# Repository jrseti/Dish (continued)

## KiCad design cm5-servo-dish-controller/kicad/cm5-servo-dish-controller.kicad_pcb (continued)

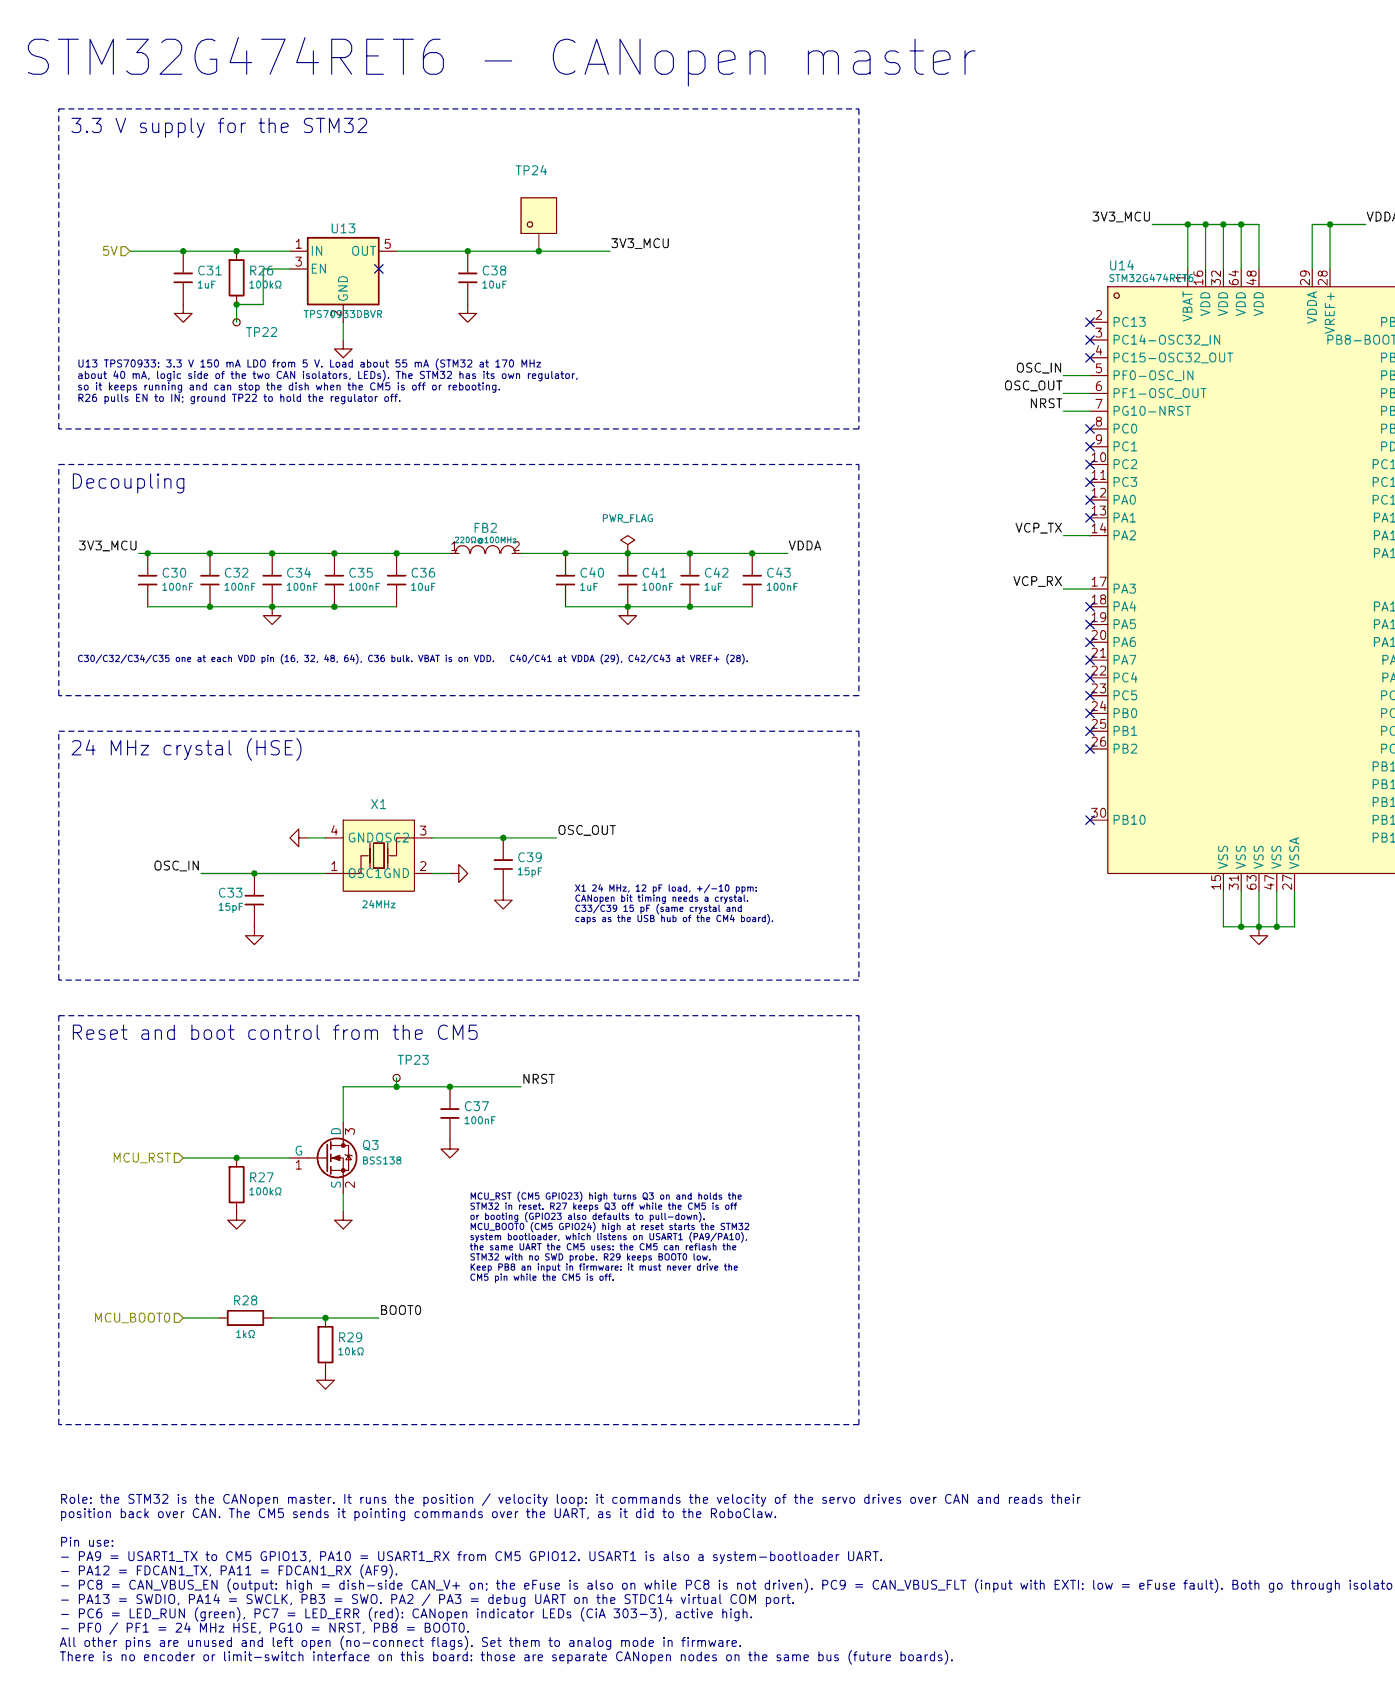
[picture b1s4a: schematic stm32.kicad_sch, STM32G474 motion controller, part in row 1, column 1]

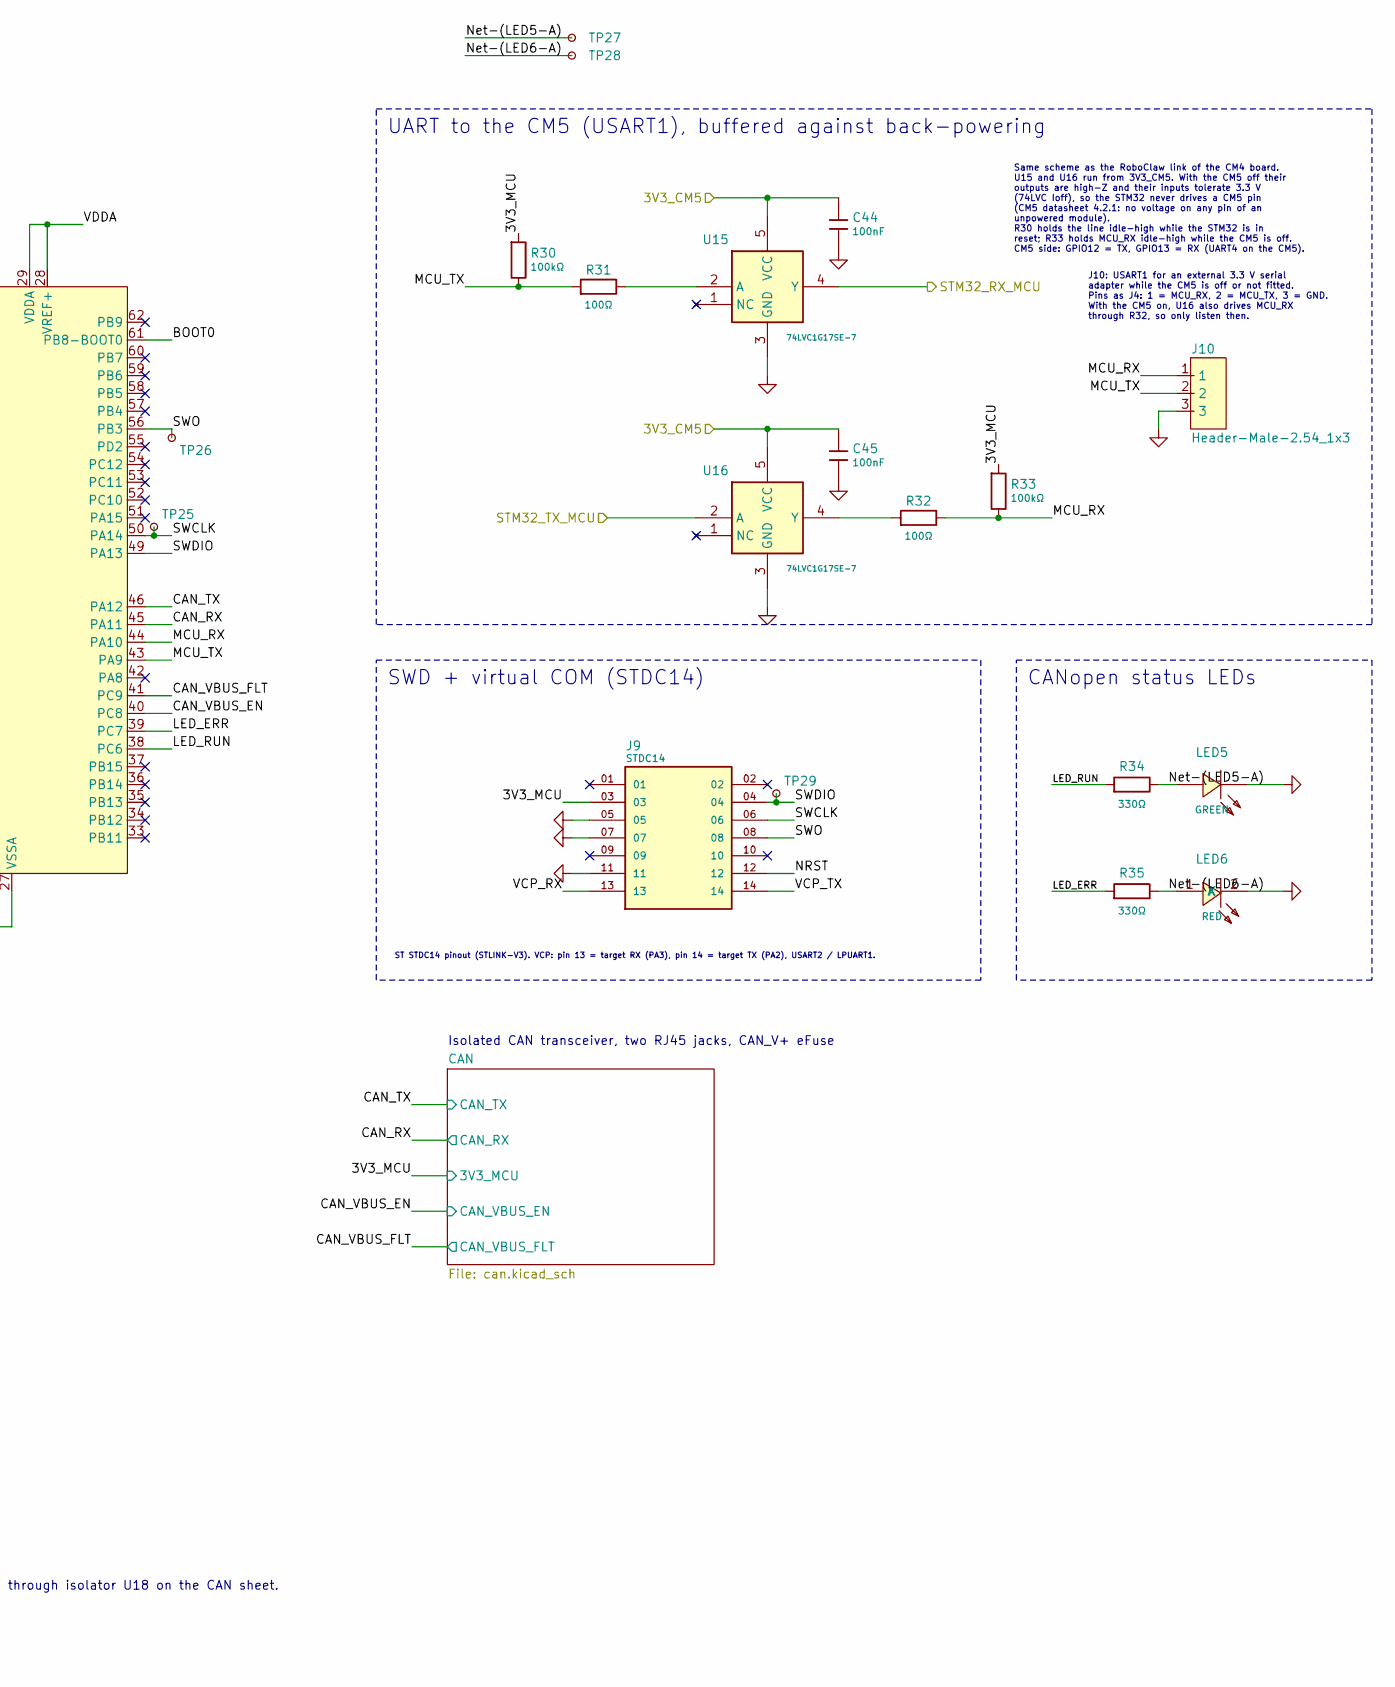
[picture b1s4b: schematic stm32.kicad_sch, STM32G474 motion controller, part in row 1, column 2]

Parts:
C30, C32, C34, C35, C37, C41, C43, C44, C45: 100nF; CAPC1005X55N; Tolerance ±10%; Voltage Rating 16V; MPN CL05B104KO5NNNC; LCSC Part C1525
C31, C40, C42: 1uF; CAPC1608X95N; Tolerance ±10%; Voltage Rating 50V; MPN CL10A105KB8NNNC; LCSC Part C15849
C33, C39: 15pF; CAPC1005X55N; Tolerance ±5%; Voltage Rating 50V; MPN 0402CG150J500NT; LCSC Part C1548
C36, C38: 10uF; CAPC1608X95N; Tolerance ±20%; Voltage Rating 25V; MPN CL10A106MA8NRNC; LCSC Part C96446
FB2: 220Ω@100MHz; INDC1608X95N; Tolerance ±25%; Current Rating 1.4A; MPN BLM18PG221SN1D; LCSC Part C80165
J9: STDC14; Samtec_FTSH-107-01-L-DV-K-A; PARTREV H; LCSC Part C5563894
J10: Header-Male-2.54_1x3; PinHeader_1x03_P2.54mm_Vertical; MPN 2.54-1*3PPin; LCSC Part C49257
LED5: GREEN; LEDC2012X110N; MPN KT-0805G; LCSC Part C2297
LED6: RED; LEDC2012X110N; MPN KT-0805R; LCSC Part C2295
Q3: BSS138; SOT95P237X112-3N; MPN BSS138; LCSC Part C7420339
R26, R27, R30, R33: 100kΩ; RESC1005X40N; Tolerance ±1%; Voltage Rating 50V; MPN 0402WGF1003TCE; LCSC Part C25741
R28: 1kΩ; RESC1005X40N; Tolerance ±1%; Voltage Rating 50V; MPN 0402WGF1001TCE; LCSC Part C11702
R29: 10kΩ; RESC1005X40N; Tolerance ±1%; Voltage Rating 50V; MPN 0402WGF1002TCE; LCSC Part C25744
R31, R32: 100Ω; RESC1005X40N; Tolerance ±1%; Voltage Rating 50V; MPN 0402WGF1000TCE; LCSC Part C25076
R34, R35: 330Ω; RESC1608X55N; Tolerance ±1%; Voltage Rating 75V; MPN 0603WAF3300T5E; LCSC Part C23138
TP22, TP23, TP25, TP26, TP27, TP28, TP29: TestPoint_Small; TestPoint_Pad_D0.8mm
TP24: 3V3_MCU; Ronghe_RH-5016; MPN RH-5016; LCSC Part C5199799
U13: TPS70933DBVR; SOT95P280X145-5N; MPN TPS70933DBVR; LCSC Part C89347
U14: STM32G474RET6; QFP50P1200X1200X160-64N; MPN STM32G474RET6; LCSC Part C521608
U15, U16: 74LVC1G17SE-7; SOT65P210X110-5N; MPN 74LVC1G17SE-7; LCSC Part C212314
X1: 24MHz; OSCCC320X250X80-4N; Frequency Tolerance ±10ppm; MPN X322524MOB4SI; LCSC Part C70590

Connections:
/3V3_CM5: C44.1, C45.1, U15.5 (VCC), U16.5 (VCC); also elsewhere on the board
/5V: C31.1, R26.1, U13.1 (IN); also elsewhere on the board
/CM5/MCU_BOOT0: R28.1; also elsewhere on the board
/CM5/MCU_RST: Q3.1 (G), R27.1; also elsewhere on the board
/CM5/STM32_RX_MCU: U15.4 (Y); also elsewhere on the board
/CM5/STM32_TX_MCU: U16.2 (A); also elsewhere on the board
/STM32/3V3_MCU: C30.1, C32.1, C34.1, C35.1, C36.1, C38.1, FB2.1, J9.03, R30.1, R33.1, TP24.1 (1_1), U13.5 (OUT), U14.1 (VBAT), U14.16 (VDD), U14.32 (VDD), U14.48 (VDD), U14.64 (VDD); also elsewhere on the board
/STM32/BOOT0: R28.2, R29.1, U14.61 (PB8-BOOT0)
/STM32/CAN_RX: U14.45 (PA11); also elsewhere on the board
/STM32/CAN_TX: U14.46 (PA12); also elsewhere on the board
/STM32/CAN_VBUS_EN: U14.40 (PC8); also elsewhere on the board
/STM32/CAN_VBUS_FLT: U14.41 (PC9); also elsewhere on the board
/STM32/LED_ERR: R35.1, U14.39 (PC7)
/STM32/LED_RUN: R34.1, U14.38 (PC6)
/STM32/MCU_RX: J10.1, R32.2, R33.2, U14.44 (PA10)
/STM32/MCU_TX: J10.2, R30.2, R31.1, U14.43 (PA9)
/STM32/NRST: C37.1, J9.12, Q3.3 (D), TP23.1 (1_1), U14.7 (PG10-NRST)
/STM32/Net-(LED5-A): LED5.1 (A), R34.2, TP27.1 (1_1)
/STM32/Net-(LED6-A): LED6.1 (A), R35.2, TP28.1 (1_1)
/STM32/OSC_IN: C33.1, U14.5 (PF0-OSC_IN), X1.1 (OSC1)
/STM32/OSC_OUT: C39.1, U14.6 (PF1-OSC_OUT), X1.3 (OSC2)
/STM32/SWCLK: J9.06, TP25.1 (1_1), U14.50 (PA14)
/STM32/SWDIO: J9.04, TP29.1 (1_1), U14.49 (PA13)
/STM32/SWO: J9.08, TP26.1 (1_1), U14.56 (PB3)
/STM32/VCP_RX: J9.13, U14.17 (PA3)
/STM32/VCP_TX: J9.14, U14.14 (PA2)
/STM32/VDDA: C40.1, C41.1, C42.1, C43.1, FB2.2, U14.28 (VREF+), U14.29 (VDDA)
GND: C30.2, C31.2, C32.2, C33.2, C34.2, C35.2, C36.2, C37.2, C38.2, C39.2, C40.2, C41.2, C42.2, C43.2, C44.2, C45.2, J9.05, J9.07, J9.11, J10.3, LED5.2 (K), LED6.2 (K), Q3.2 (S), R27.2, R29.2, U13.2 (GND), U14.15 (VSS), U14.27 (VSSA), U14.31 (VSS), U14.47 (VSS), U14.63 (VSS), U15.3 (GND), U16.3 (GND), X1.2 (GND), X1.4 (GND); also elsewhere on the board
unnamed: R26.2, TP22.1 (1_1), U13.3 (EN)
unnamed: R31.2, U15.2 (A)
unnamed: R32.1, U16.4 (Y)

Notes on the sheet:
MCU_RST (CM5 GPIO23) high turns Q3 on and holds the STM32 in reset. R27 keeps Q3 off while the CM5 is off or booting (GPIO23 also defaults to pull-down). MCU_BOOT0 (CM5 GPIO24) high at reset starts the STM32 system bootloader, which listens on USART1 (PA9/PA10), the same UART the CM5 uses: the CM5 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
C30/C32/C34/C35 one at each VDD pin (16, 32, 48, 64), C36 bulk. VBAT is on VDD. C40/C41 at VDDA (29), C42/C43 at VREF+ (28).
Isolated CAN transceiver, two RJ45 jacks, CAN_V+ eFuse
X1 24 MHz, 12 pF load, +/-10 ppm: CANopen bit timing needs a crystal. C33/C39 15 pF (same crystal and caps as the USB hub of the CM4 board).
U13 TPS70933: 3.3 V 150 mA LDO from 5 V. Load about 55 mA (STM32 at 170 MHz about 40 mA, logic side of the two CAN isolators, LEDs). The STM32 has its own regulator, so it keeps running and can stop the dish when the CM5 is off or rebooting. R26 pulls EN to IN; ground TP22 to hold the regulator off.
Role: the STM32 is the CANopen master. It runs the position / velocity loop: it commands the velocity of the servo drives over CAN and reads their position back over CAN. The CM5 sends it pointing commands over the UART, as it did to the RoboClaw. Pin use: - PA9 = USART1_TX to CM5 GPIO13, PA10 = US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
CANopen status LEDs
UART to the CM5 (USART1), buffered against back-powering
Reset and boot control from the CM5
24 MHz crystal (HSE)
ST STDC14 pinout (STLINK-V3). VCP: pin 13 = target RX (PA3), pin 14 = target TX (PA2), USART2 / LPUART1.
STM32G474RET6 - CANopen master
3.3 V supply for the STM32
Same scheme as the RoboClaw link of the CM4 board. U15 and U16 run from 3V3_CM5. With the CM5 off their outputs are high-Z and their inputs tolerate 3.3 V (74LVC Ioff), so the STM32 never drives a CM5 pin (CM5 datasheet 4.2.1: no voltage on any pin of an unpowered module). R30 holds the line idle-h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
Decoupling
SWD + virtual COM (STDC14)
J10: USART1 for an external 3.3 V serial adapter while the CM5 is off or not fitted. Pins as J4: 1 = MCU_RX, 2 = MCU_TX, 3 = GND. With the CM5 on, U16 also drives MCU_RX through R32, so only listen then.

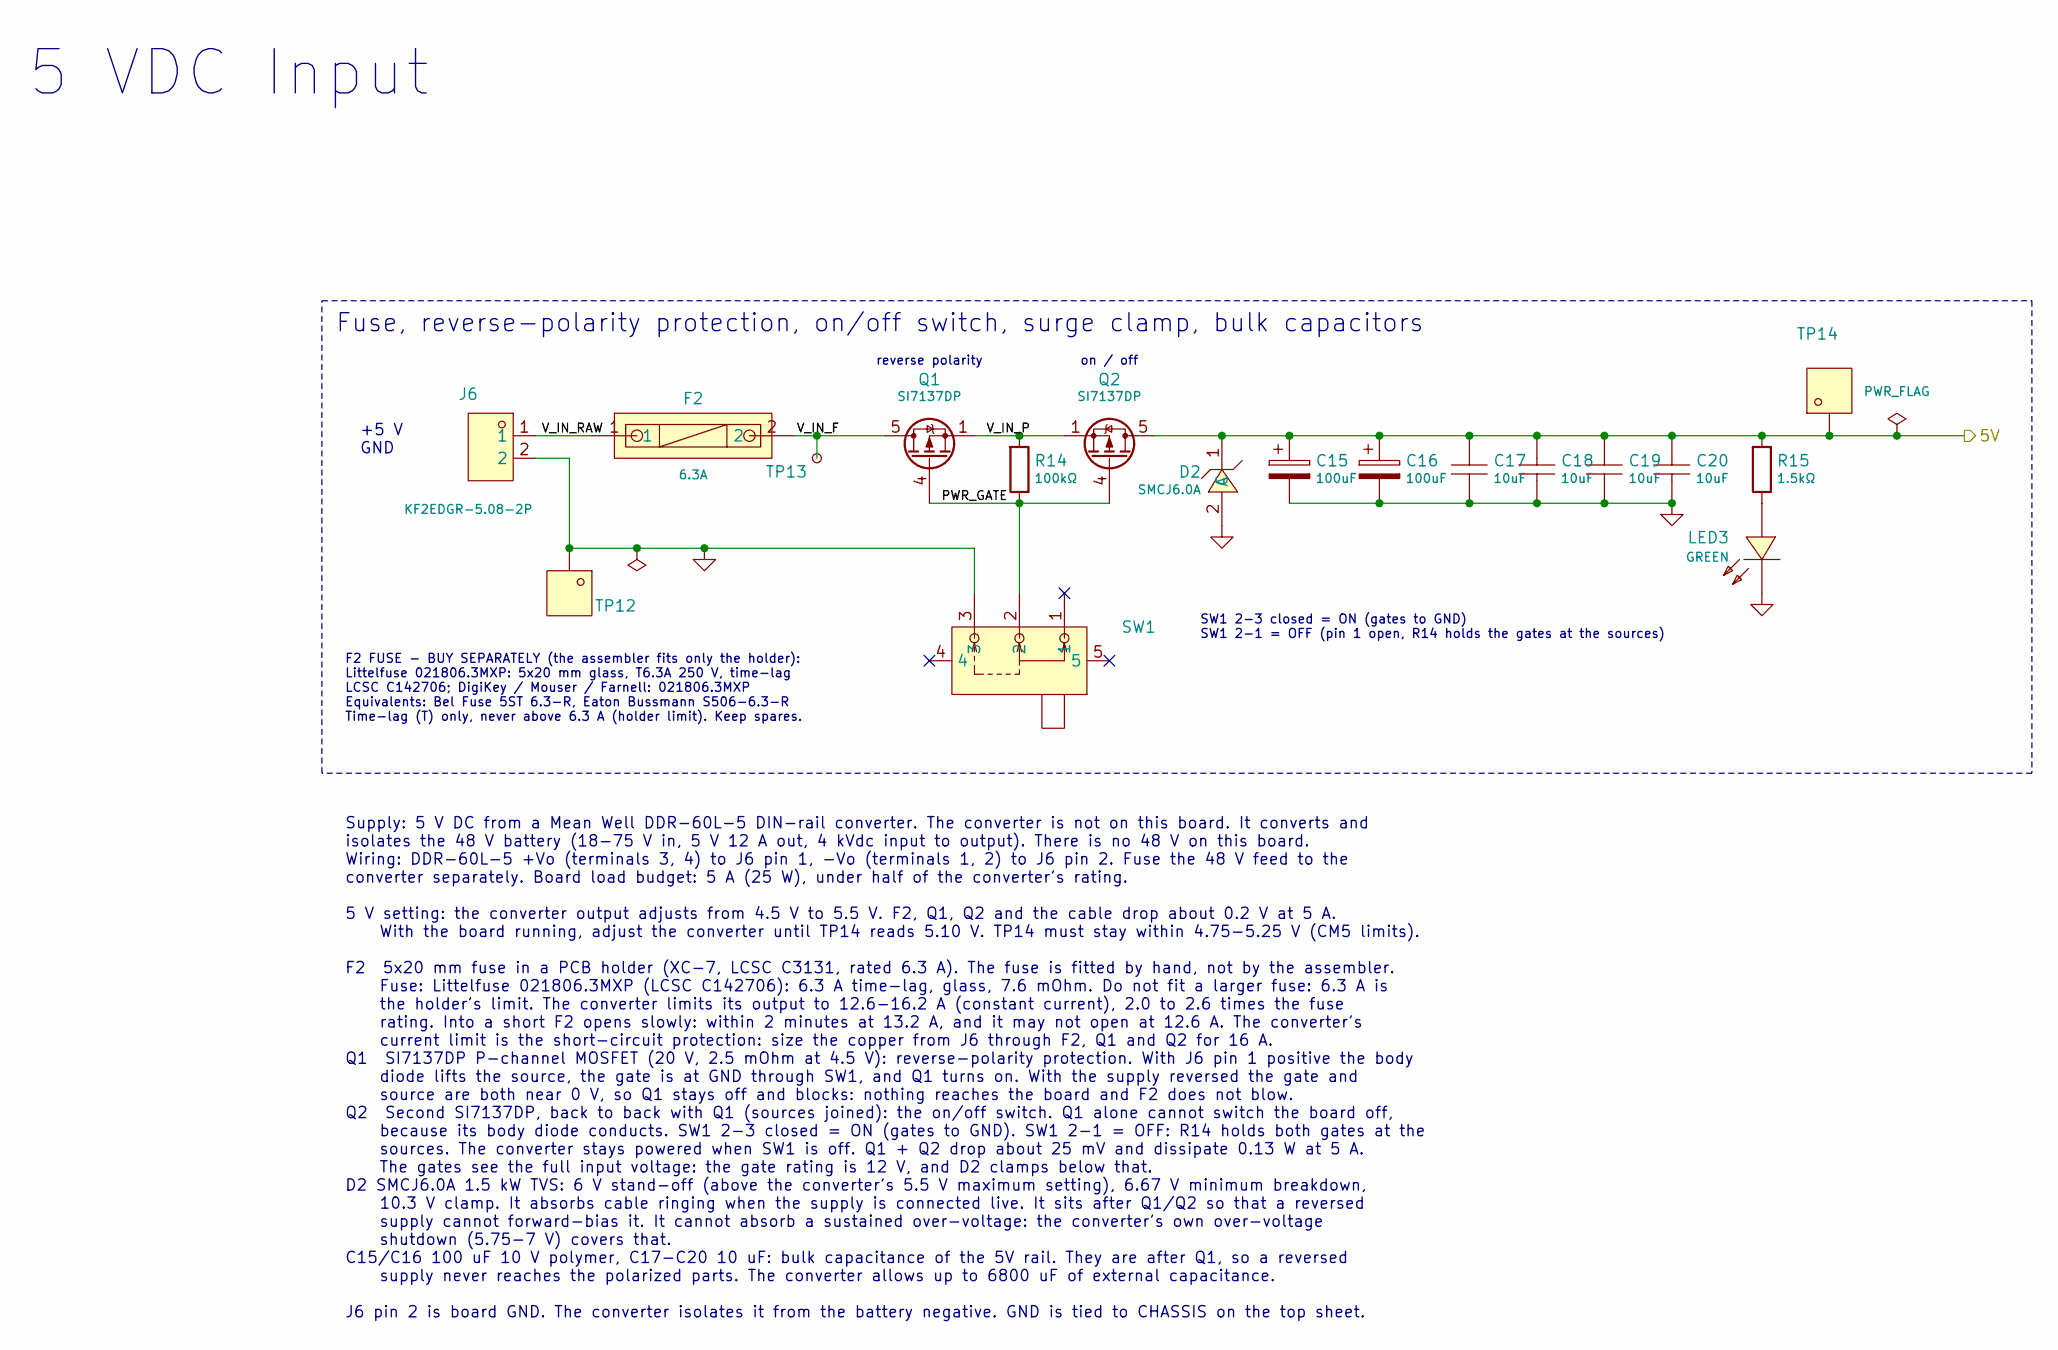
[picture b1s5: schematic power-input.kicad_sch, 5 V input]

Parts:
C15, C16: 100uF; CAPMP7343X310N; Tolerance ±20%; Voltage Rating 10V; MPN SA11AM101A19R15XXX; LCSC Part C135491
C17, C18, C19, C20: 10uF; CAPC2012X145N; Tolerance ±10%; Voltage Rating 10V; MPN CL21B106KPQNNNE; LCSC Part C32635
D2: SMCJ6.0A; DIOM7959X262N; MPN SMCJ6.0A/TR13; LCSC Part C310065
F2: 6.3A; Xucheng_XC-7_5x20; Voltage Rating 250V; Interrupting Rating 63A @ 250VAC; MPN 5x20 BLX-A XC-7; LCSC Part C3131
J6: KF2EDGR-5.08-2P; KEFA_KF2EDGR-5.08-2P; MPN KF2EDGR-5.08-2P; LCSC Part C441204
LED3: GREEN; LEDC2012X110N; MPN KT-0805G; LCSC Part C2297
Q1, Q2: SI7137DP; SON127P615X515X120-9N; MPN SI7137DP-T1-GE3; LCSC Part C784367
R14: 100kΩ; RESC1005X40N; Tolerance ±1%; Voltage Rating 50V; MPN 0402WGF1003TCE; LCSC Part C25741
R15: 1.5kΩ; RESC1005X40N; Tolerance ±1%; Voltage Rating 50V; MPN 0402WGF1501TCE; LCSC Part C25867
SW1: SS-12F49-G050; G-Switch_SS-12F49-G050; MPN SS-12F49-G050; LCSC Part C2876010
TP12: GND; Ronghe_RH-5016; MPN RH-5016; LCSC Part C5199799
TP13: TestPoint_Small; TestPoint_Pad_D0.8mm
TP14: 5V; Ronghe_RH-5016; MPN RH-5016; LCSC Part C5199799

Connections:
/5V: C15.1, C16.1, C17.1, C18.1, C19.1, C20.1, D2.1 (C), Q2.5 (D), Q2.6 (D), Q2.7 (D), Q2.8 (D), Q2.9 (D), R15.1, TP14.1 (1_1); also elsewhere on the board
/power-input/PWR_GATE: Q1.4 (G), Q2.4 (G), R14.2, SW1.2
/power-input/V_IN_F: F2.2, Q1.5 (D), Q1.6 (D), Q1.7 (D), Q1.8 (D), Q1.9 (D), TP13.1 (1_1)
/power-input/V_IN_P: Q1.1 (S), Q1.2 (S), Q1.3 (S), Q2.1 (S), Q2.2 (S), Q2.3 (S), R14.1
/power-input/V_IN_RAW: F2.1, J6.1
GND: C15.2, C16.2, C17.2, C18.2, C19.2, C20.2, D2.2 (A), J6.2, LED3.2 (K), SW1.3, TP12.1 (1_1); also elsewhere on the board
unnamed: LED3.1 (A), R15.2

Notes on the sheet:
on / off
+5 V GND
Supply: 5 V DC from a Mean Well DDR-60L-5 DIN-rail converter. The converter is not on this board. It converts and isolates the 48 V battery (18-75 V in, 5 V 12 A out, 4 kVdc input to output). There is no 48 V on this board. Wiring: DDR-60L-5 +Vo (terminals 3, 4) to J6 pin 1, -Vo (terminals 1, 2) to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
Fuse, reverse-polarity protection, on/off switch, surge clamp, bulk capacitors
5 VDC Input
SW1 2-3 closed = ON (gates to GND) SW1 2-1 = OFF (pin 1 open, R14 holds the gates at the sources)
reverse polarity
F2 FUSE - BUY SEPARATELY (the assembler fits only the holder): Littelfuse 021806.3MXP: 5x20 mm glass, T6.3A 250 V, time-lag LCSC C142706; DigiKey / Mouser / Farnell: 021806.3MXP Equivalents: Bel Fuse 5ST 6.3-R, Eaton Bussmann S506-6.3-R Time-lag (T) only, never above 6.3 A (holder limit). Keep spar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

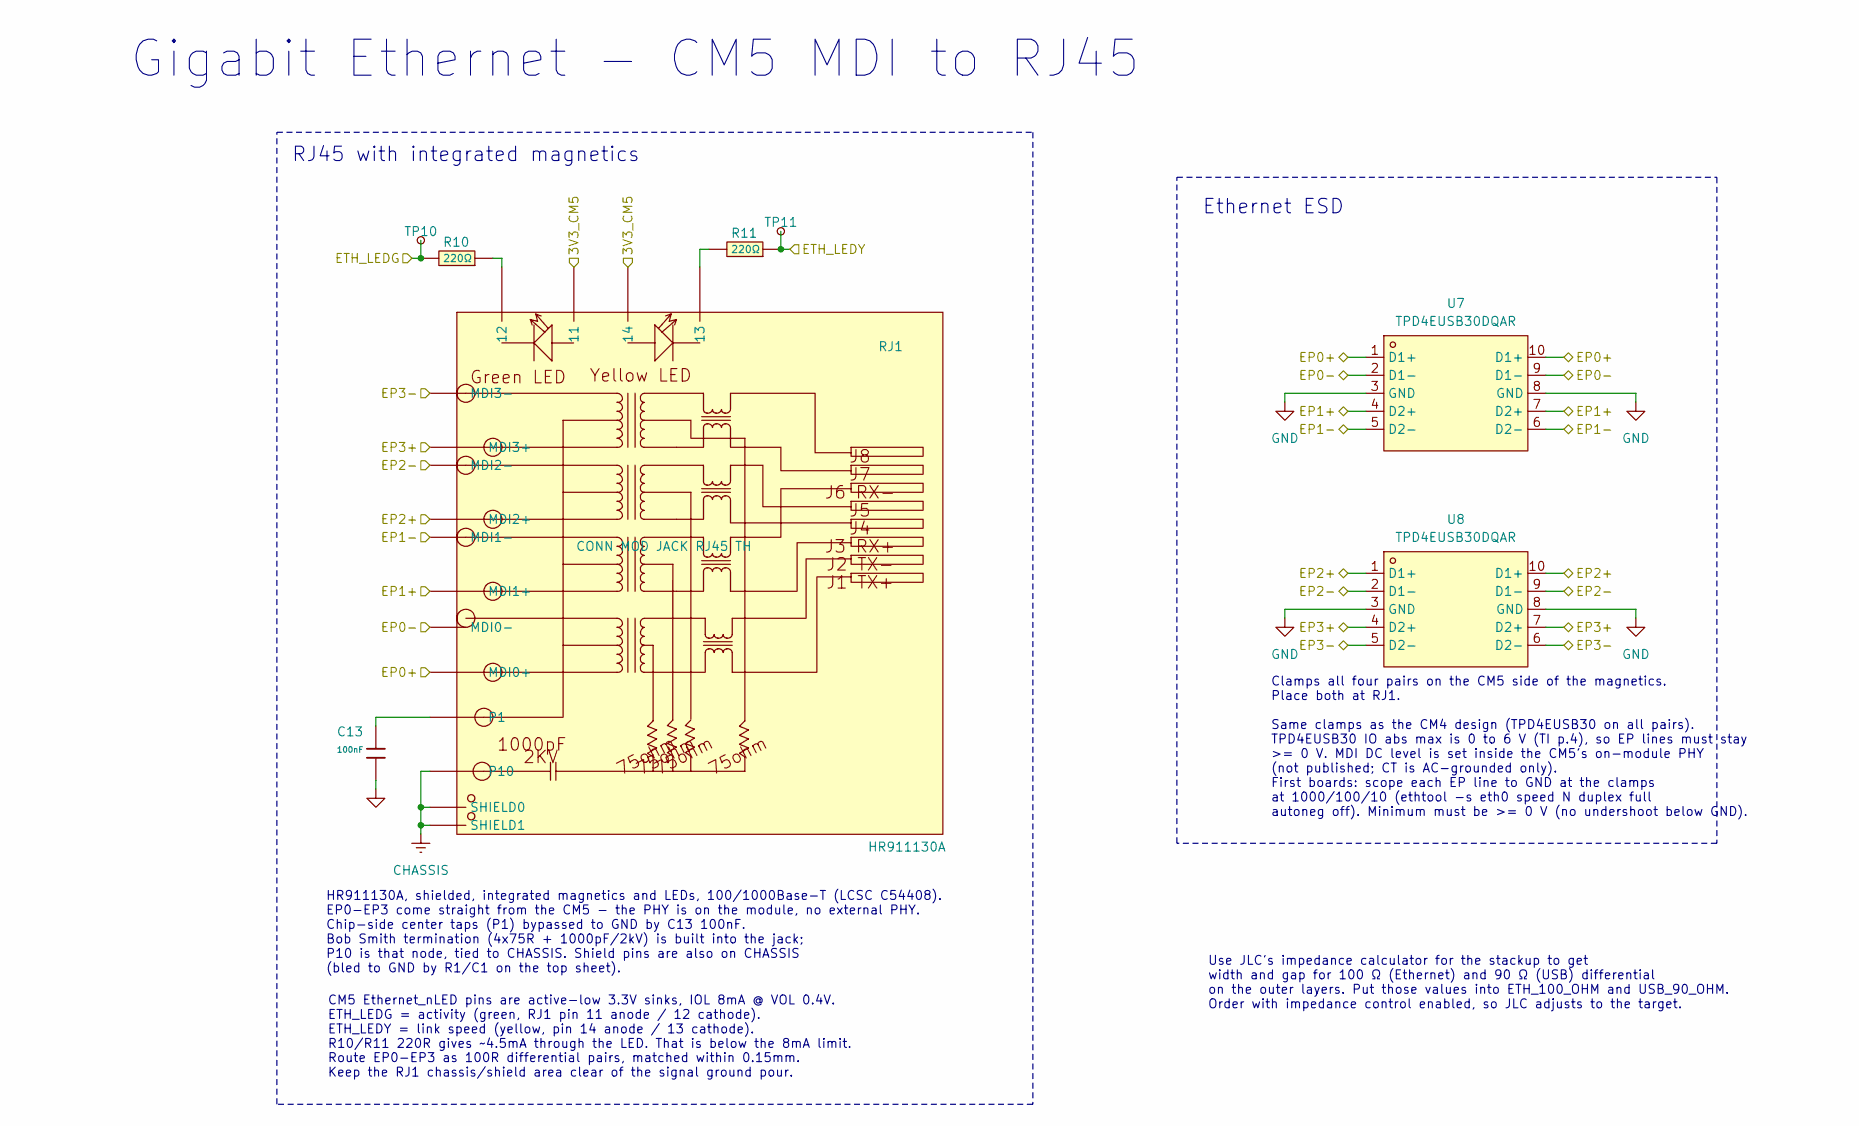
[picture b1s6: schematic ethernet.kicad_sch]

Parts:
C13: 100nF; CAPC1005X55N; Tolerance ±10%; Voltage Rating 16V; MPN CL05B104KO5NNNC; LCSC Part C1525
R10, R11: 220Ω; RESC1005X40N; Tolerance ±1%; Voltage Rating 50V; MPN 0402WGF2200TCE; LCSC Part C25091
RJ1: HR911130A; HanRun_HR911130A; MPN HR911130A; LCSC Part C54408
TP10, TP11: TestPoint_Small; TestPoint_Pad_D0.8mm
U7, U8: TPD4EUSB30DQAR; SON50P100X250X60-10N; MPN TPD4EUSB30DQAR; LCSC Part C90627

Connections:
/3V3_CM5: RJ1.11, RJ1.14; also elsewhere on the board
/CM5/EP0+: RJ1.P2 (MDI0+), U7.1 (D1+), U7.10 (D1+); also elsewhere on the board
/CM5/EP0-: RJ1.P3 (MDI0-), U7.2 (D1-), U7.9 (D1-); also elsewhere on the board
/CM5/EP1+: RJ1.P4 (MDI1+), U7.4 (D2+), U7.7 (D2+); also elsewhere on the board
/CM5/EP1-: RJ1.P7 (MDI1-), U7.5 (D2-), U7.6 (D2-); also elsewhere on the board
/CM5/EP2+: RJ1.P5 (MDI2+), U8.1 (D1+), U8.10 (D1+); also elsewhere on the board
/CM5/EP2-: RJ1.P6 (MDI2-), U8.2 (D1-), U8.9 (D1-); also elsewhere on the board
/CM5/EP3+: RJ1.P8 (MDI3+), U8.4 (D2+), U8.7 (D2+); also elsewhere on the board
/CM5/EP3-: RJ1.P9 (MDI3-), U8.5 (D2-), U8.6 (D2-); also elsewhere on the board
/CM5/ETH_LEDG: R10.2, TP10.1 (1_1); also elsewhere on the board
/CM5/ETH_LEDY: R11.1, TP11.1 (1_1); also elsewhere on the board
CHASSIS: RJ1.P10, RJ1.SHIELD0, RJ1.SHIELD1; also elsewhere on the board
GND: C13.2, U7.3 (GND), U7.8 (GND), U8.3 (GND), U8.8 (GND); also elsewhere on the board
unnamed: C13.1, RJ1.P1
unnamed: R10.1, RJ1.12
unnamed: R11.2, RJ1.13

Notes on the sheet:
Ethernet ESD
Use JLC's impedance calculator for the stackup to get width and gap for 100 Ω (Ethernet) and 90 Ω (USB) differential on the outer layers. Put those values into ETH_100_OHM and USB_90_OHM. Order with impedance control enabled, so JLC adjusts to the target.
HR911130A, shielded, integrated magnetics and LEDs, 100/1000Base-T (LCSC C54408). EP0-EP3 come straight from the CM5 - the PHY is on the module, no external PHY. Chip-side center taps (P1) bypassed to GND by C13 100nF. Bob Smith termination (4x75R + 1000pF/2kV) is built into the jack; P10 is that n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
RJ45 with integrated magnetics
Clamps all four pairs on the CM5 side of the magnetics. Place both at RJ1. Same clamps as the CM4 design (TPD4EUSB30 on all pairs). TPD4EUSB30 IO abs max is 0 to 6 V (TI p.4), so EP lines must stay >= 0 V. MDI DC level is set inside the CM5's on-module PHY (not published; CT is AC-grounded only). F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
Route EP0-EP3 as 100R differential pairs, matched within 0.15mm. Keep the RJ1 chassis/shield area clear of the signal ground pour.
CM5 Ethernet_nLED pins are active-low 3.3V sinks, IOL 8mA @ VOL 0.4V. ETH_LEDG = activity (green, RJ1 pin 11 anode / 12 cathode). ETH_LEDY = link speed (yellow, pin 14 anode / 13 cathode). R10/R11 220R gives ~4.5mA through the LED. That is below the 8mA limit.
Gigabit Ethernet - CM5 MDI to RJ45

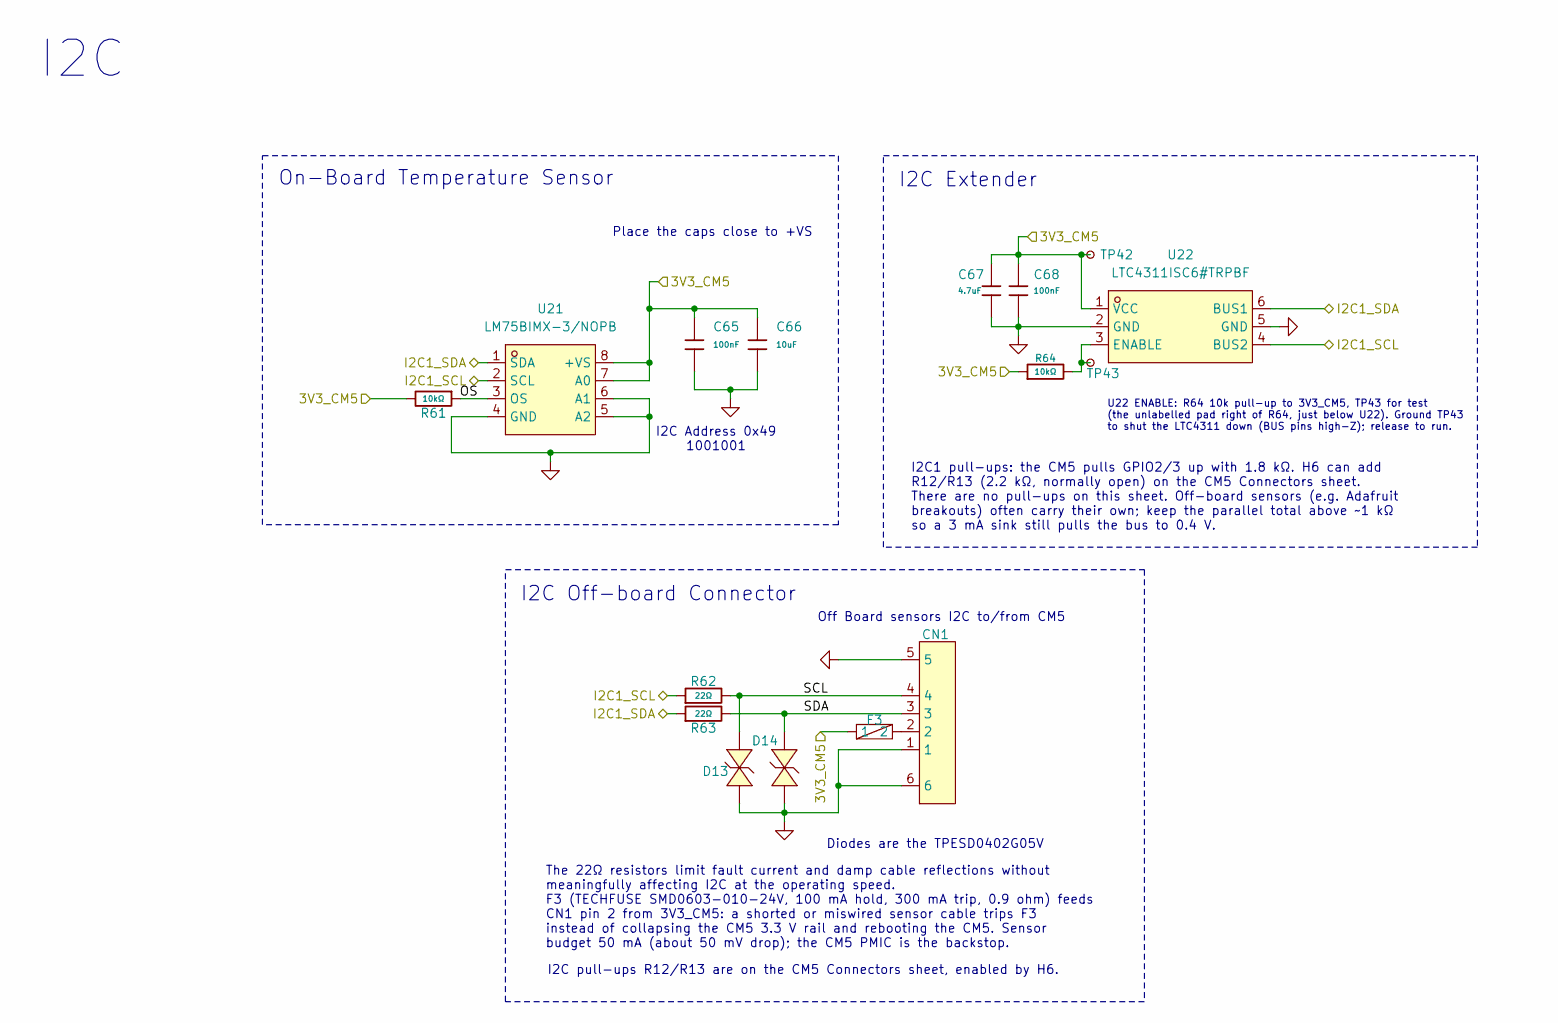
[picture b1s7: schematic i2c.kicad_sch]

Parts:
C65, C68: 100nF; CAPC1005X55N; Tolerance ±10%; Voltage Rating 16V; MPN CL05B104KO5NNNC; LCSC Part C1525
C66: 10uF; CAPC1608X95N; Tolerance ±10%; Voltage Rating 10V; MPN CL10A106KP8NNNC; LCSC Part C19702
C67: 4.7uF; CAPC1005X55N; Tolerance ±20%; Voltage Rating 10V; MPN CL05A475MP5NRNC; LCSC Part C23733
CN1: SM04B-SRSS-TB (LF)(SN); JST_SH_SM04B-SRSS-TB_1x04-1MP_P1.00mm_Horizontal; MPN SM04B-SRSS-TB(LF)(SN); LCSC Part C160404
D13, D14: TPESD0402G05V; DIOC1005X55N; MPN TPESD0402G05V; LCSC Part C558615
F3: 100mA; FUSC1608X100N; MPN SMD0603-010-24V; LCSC Part C70048
R61, R64: 10kΩ; RESC1005X40N; Tolerance ±1%; Voltage Rating 50V; MPN 0402WGF1002TCE; LCSC Part C25744
R62, R63: 22Ω; RESC1005X40N; Tolerance ±1%; Voltage Rating 50V; MPN 0402WGF220JTCE; LCSC Part C25092
TP42, TP43: TestPoint_Small; TestPoint_Pad_D0.8mm
U21: LM75BIMX-3/NOPB; SOIC127P600X175-8N; MPN LM75BIMX-3/NOPB; LCSC Part C477980
U22: LTC4311ISC6#TRPBF; SOT65P210X110-6N; MPN LTC4311ISC6#TRPBF; LCSC Part C688097

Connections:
/3V3_CM5: C65.1, C66.1, C67.1, C68.1, F3.1, R61.2, R64.1, TP42.1 (1_1), U21.7 (A0), U21.8 (+VS), U22.1 (VCC); also elsewhere on the board
/CM5/I2C1_SCL: R62.1, U21.2 (SCL), U22.4 (BUS2); also elsewhere on the board
/CM5/I2C1_SDA: R63.1, U21.1 (SDA), U22.6 (BUS1); also elsewhere on the board
/CM5/I2C/OS: R61.1, U21.3 (OS)
/CM5/I2C/SCL: CN1.4, D13.1 (K), R62.2
/CM5/I2C/SDA: CN1.3, D14.1 (K), R63.2
GND: C65.2, C66.2, C67.2, C68.2, CN1.1, CN1.5, CN1.6, D13.2 (A), D14.2 (A), U21.4 (GND), U21.5 (A2), U21.6 (A1), U22.2 (GND), U22.5 (GND); also elsewhere on the board
unnamed: CN1.2, F3.2
unnamed: R64.2, TP43.1 (1_1), U22.3 (ENABLE)

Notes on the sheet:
I2C1 pull-ups: the CM5 pulls GPIO2/3 up with 1.8 kΩ. H6 can add R12/R13 (2.2 kΩ, normally open) on the CM5 Connectors sheet. There are no pull-ups on this sheet. Off-board sensors (e.g. Adafruit breakouts) often carry their own; keep the parallel total above ~1 kΩ so a 3 mA sink still pulls the bus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
I2C pull-ups R12/R13 are on the CM5 Connectors sheet, enabled by H6.
Diodes are the TPESD0402G05V
Place the caps close to +VS
I2C Address 0x49 1001001
I2C
The 22Ω resistors limit fault current and damp cable reflections without meaningfully affecting I2C at the operating speed. F3 (TECHFUSE SMD0603-010-24V, 100 mA hold, 300 mA trip, 0.9 ohm) feeds CN1 pin 2 from 3V3_CM5: a shorted or miswired sensor cable trips F3 instead of collapsing the CM5 3.3 V 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
U22 ENABLE: R64 10k pull-up to 3V3_CM5, TP43 for test (the unlabelled pad right of R64, just below U22). Ground TP43 to shut the LTC4311 down (BUS pins high-Z); release to run.
I2C Extender
I2C Off-board Connector
Off Board sensors I2C to/from CM5
On-Board Temperature Sensor
